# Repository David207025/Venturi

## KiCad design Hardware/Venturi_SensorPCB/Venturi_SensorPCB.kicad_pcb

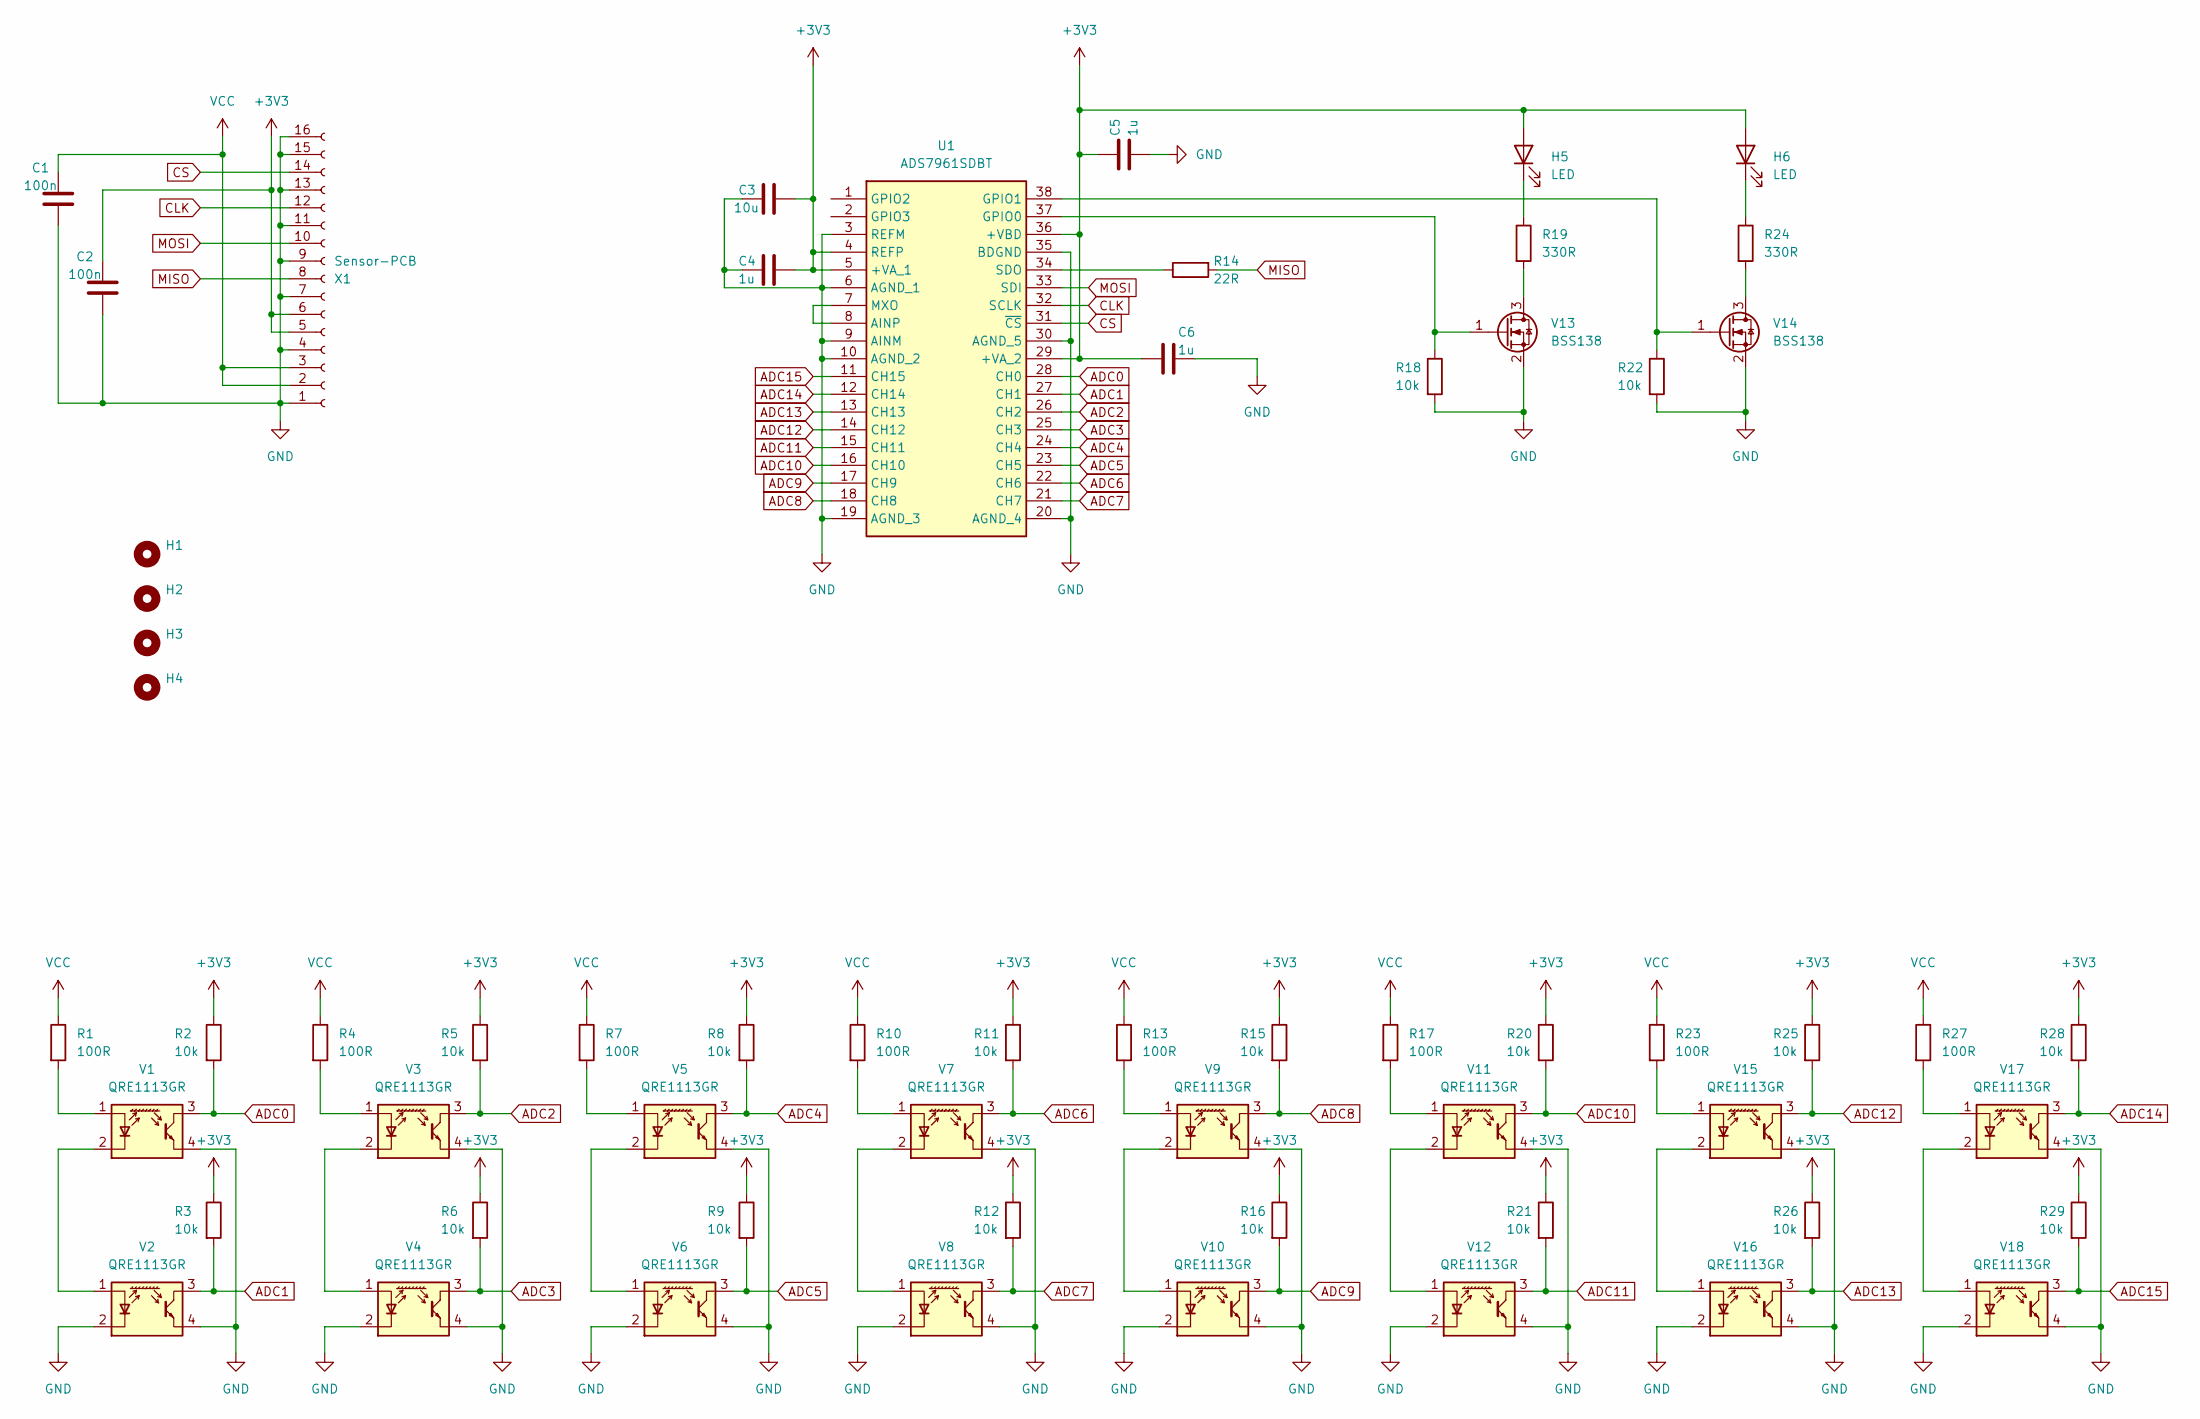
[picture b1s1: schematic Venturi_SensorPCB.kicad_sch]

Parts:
C1, C2: 100n; C_0805_2012Metric_Pad1.18x1.45mm_HandSolder
C3: 10u; C_0603_1608Metric_Pad1.08x0.95mm_HandSolder
C4, C5, C6: 1u; C_0603_1608Metric_Pad1.08x0.95mm_HandSolder
H1, H2, H3, H4: MountingHole_3.2mm_M3_DIN965
H5, H6: LED; LED_0805_2012Metric_Pad1.15x1.40mm_HandSolder
R1, R4, R7, R10, R13, R17, R23, R27: 100R; R_0603_1608Metric_Pad0.98x0.95mm_HandSolder
R2, R3, R5, R6, R8, R9, R11, R12, R15, R16, R18, R20, R21, R22, R25, R26, R28, R29: 10k; R_0603_1608Metric_Pad0.98x0.95mm_HandSolder
R14: 22R; R_0805_2012Metric_Pad1.20x1.40mm_HandSolder
R19, R24: 330R; R_0603_1608Metric_Pad0.98x0.95mm_HandSolder
U1: ADS7961SDBT; SOP50P640X120-38N; Mouser Part Number 595-ADS7961SDBT
V1, V2, V3, V4, V5, V6, V7, V8, V9, V10, V11, V12, V15, V16, V17, V18: QRE1113GR; OnSemi_CASE100CY
V13, V14: BSS138; SOT-23
X1: Sensor-PCB; SensorPCB-Connector

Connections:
+3V3: C2.1, C3.2, C4.2, C5.1, C6.1, H5.2 (A), H6.2 (A), R2.1, R3.1, R5.1, R6.1, R8.1, R9.1, R11.1, R12.1, R15.1, R16.1, R20.1, R21.1, R25.1, R26.1, R28.1, R29.1, U1.4 (REFP), U1.5 (+VA_1), U1.29 (+VA_2), U1.36 (+VBD), X1.5, X1.6
ADC0: R2.2, U1.28 (CH0), V1.3
ADC1: R3.2, U1.27 (CH1), V2.3
ADC2: R5.2, U1.26 (CH2), V3.3
ADC3: R6.2, U1.25 (CH3), V4.3
ADC4: R8.2, U1.24 (CH4), V5.3
ADC5: R9.2, U1.23 (CH5), V6.3
ADC6: R11.2, U1.22 (CH6), V7.3
ADC7: R12.2, U1.21 (CH7), V8.3
ADC8: R15.2, U1.18 (CH8), V9.3
ADC9: R16.2, U1.17 (CH9), V10.3
ADC10: R20.2, U1.16 (CH10), V11.3
ADC11: R21.2, U1.15 (CH11), V12.3
ADC12: R25.2, U1.14 (CH12), V15.3
ADC13: R26.2, U1.13 (CH13), V16.3
ADC14: R28.2, U1.12 (CH14), V17.3
ADC15: R29.2, U1.11 (CH15), V18.3
CLK: U1.32 (SCLK), X1.12
CS: U1.31 (~CS), X1.14
GND: C1.2, C2.2, C3.1, C4.1, C5.2, C6.2, R18.2, R22.2, U1.3 (REFM), U1.6 (AGND_1), U1.9 (AINM), U1.10 (AGND_2), U1.19 (AGND_3), U1.20 (AGND_4), U1.30 (AGND_5), U1.35 (BDGND), V1.4, V2.2 (K), V2.4, V3.4, V4.2 (K), V4.4, V5.4, V6.2 (K), V6.4, V7.4, V8.2 (K), V8.4, V9.4, V10.2 (K), V10.4, V11.4, V12.2 (K), V12.4, V13.2 (S), V14.2 (S), V15.4, V16.2 (K), V16.4, V17.4, V18.2 (K), V18.4, X1.1, X1.4, X1.7, X1.9, X1.11, X1.13, X1.15, X1.16
MISO: R14.2, X1.8
MOSI: U1.33 (SDI), X1.10
unnamed: H5.1 (K), R19.1
unnamed: H6.1 (K), R24.1
unnamed: U1.7 (MXO), U1.8 (AINP)
unnamed: R18.1, U1.37 (GPIO0), V13.1 (G)
unnamed: R22.1, U1.38 (GPIO1), V14.1 (G)
unnamed: R14.1, U1.34 (SDO)
unnamed: R1.2, V1.1 (A)
unnamed: V1.2 (K), V2.1 (A)
unnamed: R4.2, V3.1 (A)
unnamed: V3.2 (K), V4.1 (A)
unnamed: R7.2, V5.1 (A)
unnamed: V5.2 (K), V6.1 (A)
unnamed: R10.2, V7.1 (A)
unnamed: V7.2 (K), V8.1 (A)
unnamed: R13.2, V9.1 (A)
unnamed: V9.2 (K), V10.1 (A)
unnamed: R17.2, V11.1 (A)
unnamed: V11.2 (K), V12.1 (A)
unnamed: R19.2, V13.3 (D)
unnamed: R24.2, V14.3 (D)
unnamed: R23.2, V15.1 (A)
unnamed: V15.2 (K), V16.1 (A)
unnamed: R27.2, V17.1 (A)
unnamed: V17.2 (K), V18.1 (A)
VCC: C1.1, R1.1, R4.1, R7.1, R10.1, R13.1, R17.1, R23.1, R27.1, X1.2, X1.3

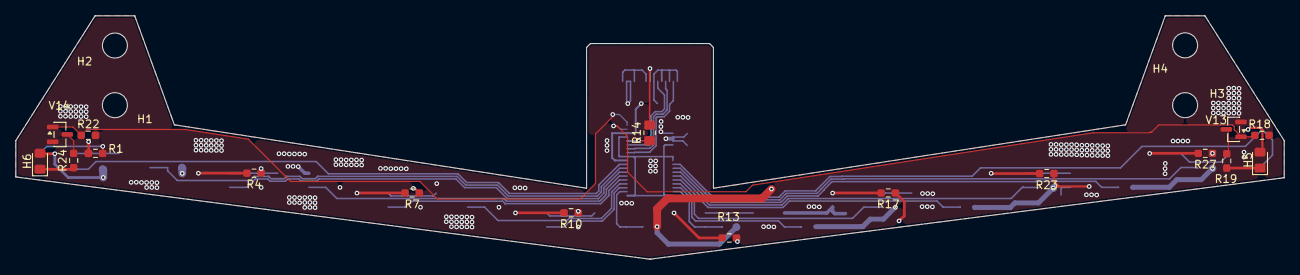
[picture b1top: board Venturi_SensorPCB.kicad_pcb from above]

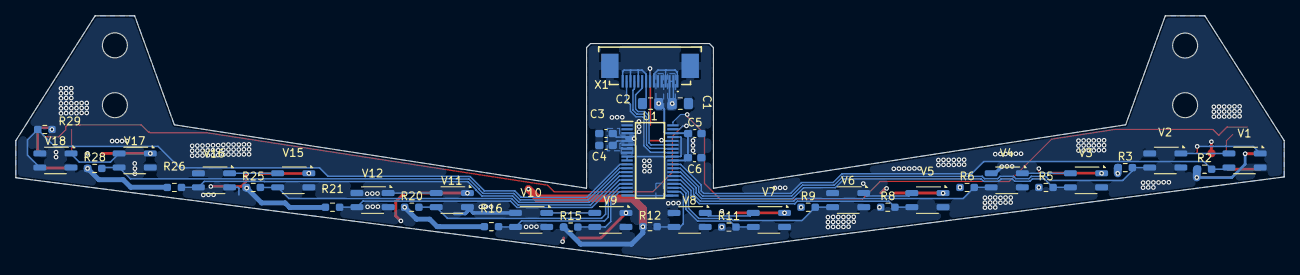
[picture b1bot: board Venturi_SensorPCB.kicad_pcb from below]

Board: 4 copper layers, 162.6 x 31.2 mm, 61 parts (40 on the bottom side), 47 nets.

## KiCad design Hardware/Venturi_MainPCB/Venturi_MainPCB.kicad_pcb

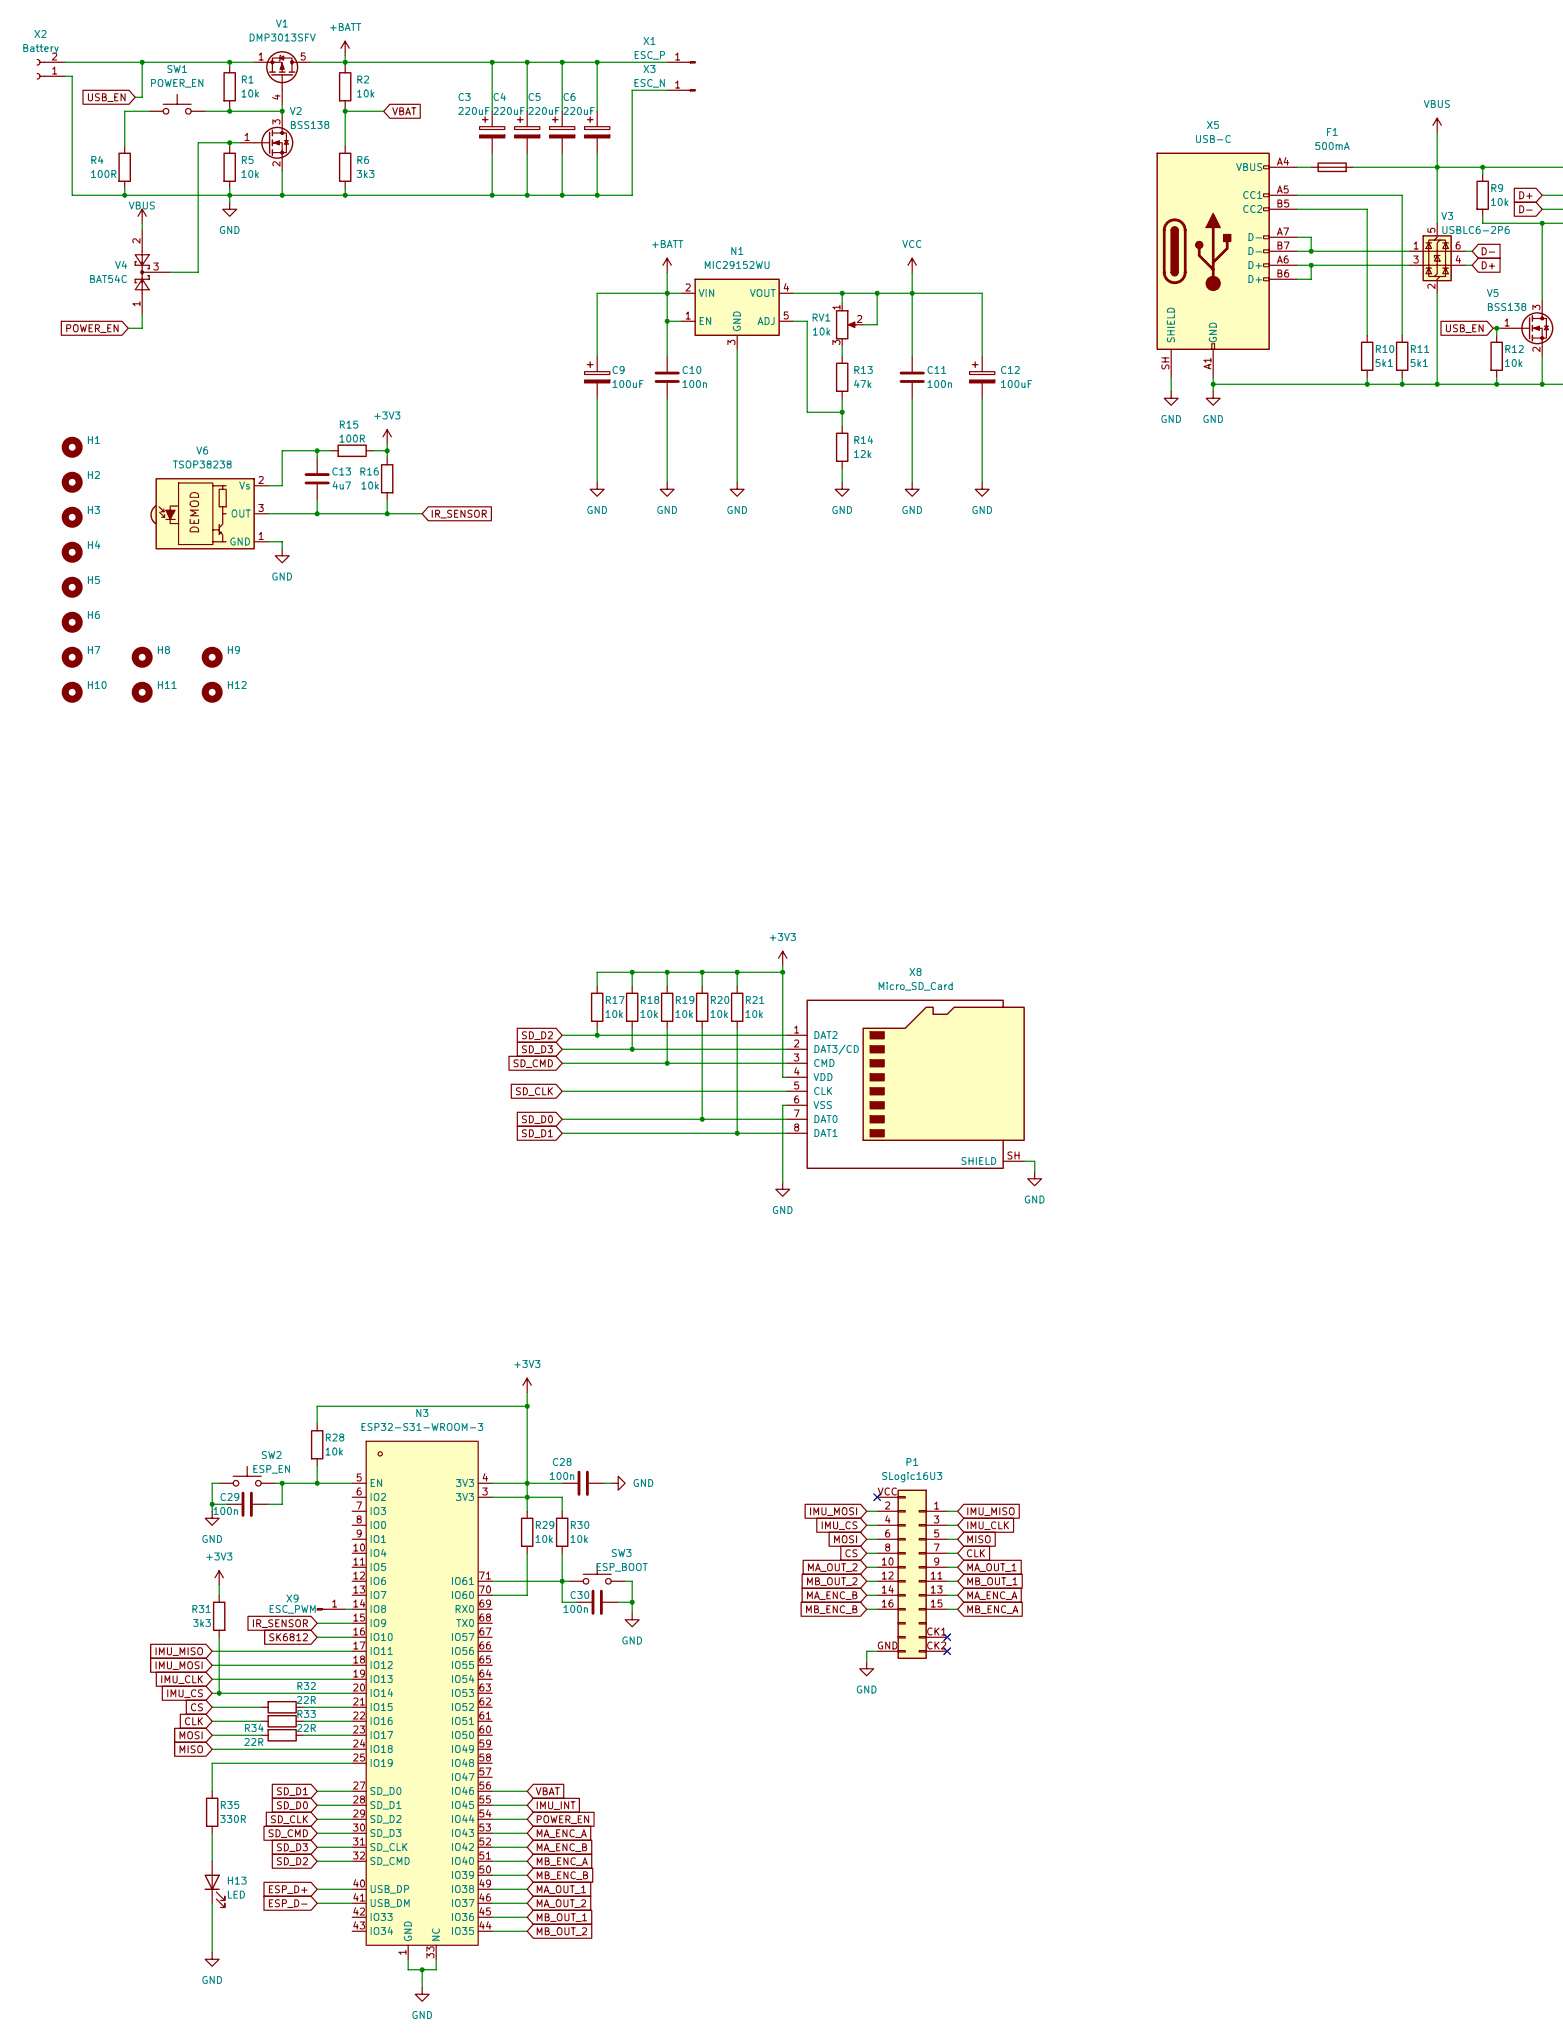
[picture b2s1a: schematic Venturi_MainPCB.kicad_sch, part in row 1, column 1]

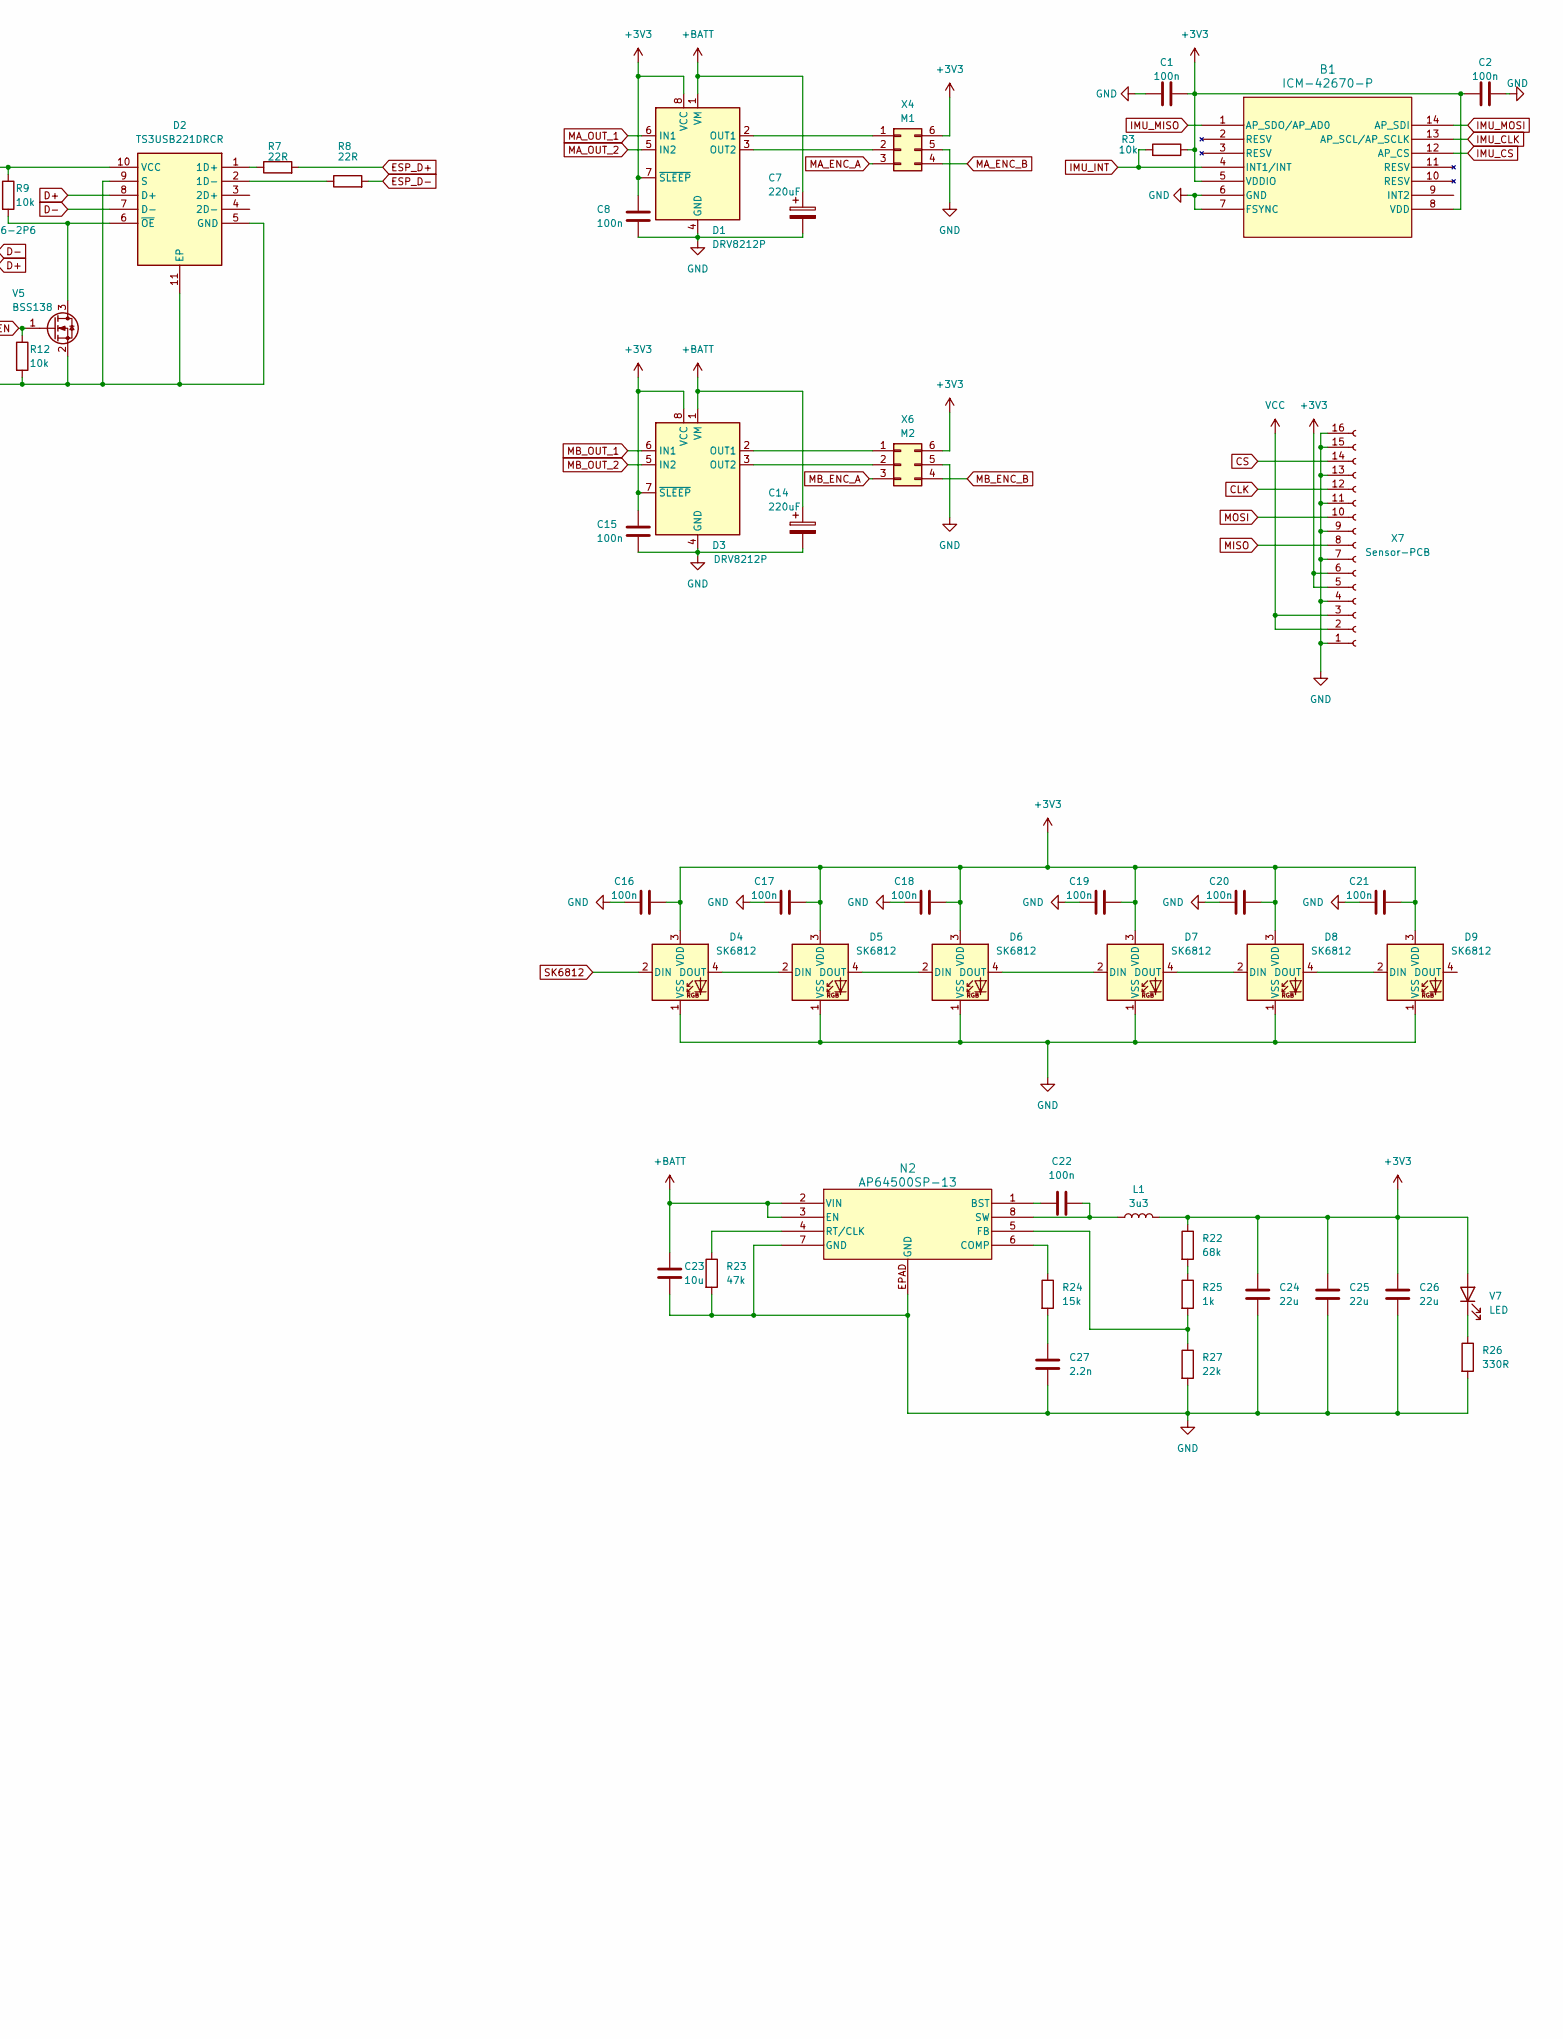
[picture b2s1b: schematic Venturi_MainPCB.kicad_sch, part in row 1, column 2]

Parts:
B1: ICM-42670-P; LGA-14_3x2.5mm_P0.5mm_LayoutBorder3x4y
C1, C2, C8, C10, C11, C15, C16, C17, C18, C19, C20, C21, C28, C29, C30: 100n; C_0805_2012Metric_Pad1.18x1.45mm_HandSolder
C3, C4, C5, C6, C7, C14: 220uF; CP_Elec_6.3x9.9
C9, C12: 100uF; CP_EIA-7343-15_Kemet-W_HandSolder
C13: 4u7; C_0805_2012Metric_Pad1.18x1.45mm_HandSolder
C22: 100n; C_0603_1608Metric_Pad1.08x0.95mm_HandSolder
C23: 10u; C_0603_1608Metric_Pad1.08x0.95mm_HandSolder
C24, C25, C26: 22u; C_0603_1608Metric_Pad1.08x0.95mm_HandSolder
C27: 2.2n; C_0603_1608Metric_Pad1.08x0.95mm_HandSolder
D1, D3: DRV8212P; WSON-8-1EP_2x2mm_P0.5mm_EP0.9x1.6mm_ThermalVias
D2: TS3USB221DRCR; SON50P300X300X100-11N-D; Mouser Part Number 595-TS3USB221DRCR
D4, D5, D6, D7, D8, D9: SK6812; LED_SK6812_PLCC4_5.0x5.0mm_P3.2mm
F1: 500mA; Fuse_0805_2012Metric_Pad1.15x1.40mm_HandSolder
H1, H2, H3, H4, H5, H6, H7, H8, H9, H10, H11, H12: MountingHole_3.2mm_M3_DIN965
H13: LED; LED_0805_2012Metric_Pad1.15x1.40mm_HandSolder
L1: 3u3; L_Vishay_IHLP-1616
N1: MIC29152WU; TO-252-5_TabPin3
N2: AP64500SP-13; SO-8EP_DIO
N3: ESP32-S31-WROOM-3; MPN ESP32-S31-WROOM-3; LCSC Part C9900281993
P1: SLogic16U3
R1, R2, R3, R5, R16, R17, R18, R19, R20, R21, R28, R29, R30: 10k; R_0805_2012Metric_Pad1.20x1.40mm_HandSolder
R4, R15: 100R; R_0805_2012Metric_Pad1.20x1.40mm_HandSolder
R6, R31: 3k3; R_0805_2012Metric_Pad1.20x1.40mm_HandSolder
R7, R8, R32, R33, R34: 22R; R_0805_2012Metric_Pad1.20x1.40mm_HandSolder
R9, R12: 10k; R_0603_1608Metric_Pad0.98x0.95mm_HandSolder
R10, R11: 5k1; R_0805_2012Metric_Pad1.20x1.40mm_HandSolder
R13: 47k; R_0805_2012Metric_Pad1.20x1.40mm_HandSolder
R14: 12k; R_0805_2012Metric_Pad1.20x1.40mm_HandSolder
R22: 68k; R_0603_1608Metric_Pad0.98x0.95mm_HandSolder
R23: 47k; R_0603_1608Metric_Pad0.98x0.95mm_HandSolder
R24: 15k; R_0603_1608Metric_Pad0.98x0.95mm_HandSolder
R25: 1k; R_0603_1608Metric_Pad0.98x0.95mm_HandSolder
R26: 330R; R_0603_1608Metric_Pad0.98x0.95mm_HandSolder
R27: 22k; R_0603_1608Metric_Pad0.98x0.95mm_HandSolder
R35: 330R; R_0805_2012Metric_Pad1.20x1.40mm_HandSolder
RV1: 10k; Potentiometer_Bourns_3314J_Vertical
SW1: POWER_EN; SW_SPST_Omron_B3FS-100xP
SW2: ESP_EN; SW_SPST_Omron_B3FS-100xP
SW3: ESP_BOOT; SW_SPST_Omron_B3FS-100xP
V1: DMP3013SFV; Diodes_PowerDI3333-8
V2, V5: BSS138; SOT-23
V3: USBLC6-2P6; SOT-666
V4: BAT54C; SOT-23
V6: TSOP38238; Vishay_CAST-3Pin
V7: LED; LED_0805_2012Metric_Pad1.15x1.40mm_HandSolder
X1: ESC_P; SolderWire-0.25sqmm_1x01_D0.65mm_OD1.7mm
X2: Battery; AMASS_XT30U-M_1x02_P5.0mm_Vertical
X3: ESC_N; SolderWire-0.25sqmm_1x01_D0.65mm_OD1.7mm
X4: M1; PinHeader_2x03_P2.54mm_Vertical_SMD
X5: USB-C; USB_C_Receptacle_G-Switch_GT-USB-7010ASV
X6: M2; PinHeader_2x03_P2.54mm_Vertical_SMD
X7: Sensor-PCB; SensorPCB-Connector
X8: Micro_SD_Card; microSD_HC_Wuerth_693072010801
X9: ESC_PWM; SolderWire-0.25sqmm_1x01_D0.65mm_OD1.7mm

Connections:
+3V3: B1.5 (VDDIO), B1.8 (VDD), C1.1, C2.2, C8.1, C15.1, C16.2, C17.2, C18.2, C19.2, C20.2, C21.2, C24.2, C25.2, C26.2, C28.1, D1.7 (~SLEEP), D1.8 (VCC), D3.7 (~SLEEP), D3.8 (VCC), D4.3 (VDD), D5.3 (VDD), D6.3 (VDD), D7.3 (VDD), D8.3 (VDD), D9.3 (VDD), L1.2, N3.3 (3V3), N3.4 (3V3), R3.1, R15.1, R16.1, R17.1, R18.1, R19.1, R20.1, R21.1, R22.1, R28.1, R29.1, R30.1, R31.1, V7.2 (A), X4.6, X6.6, X7.5, X7.6, X8.4 (VDD)
+BATT: C3.1, C4.1, C5.1, C6.1, C7.1, C9.1, C10.1, C14.1, C23.2, D1.1 (VM), D3.1 (VM), N1.1 (EN), N1.2 (VIN), N2.2 (VIN), N2.3 (EN), R2.1, V1.5 (D), X1.1 (Pin_1_1)
CLK: P1.7, R33.2, X7.12
CS: P1.8, R32.2, X7.14
D+: D2.8 (D+), V3.4 (I/O2)
D-: D2.7 (D-), V3.6 (I/O1)
ESP_D+: N3.40 (USB_DP), R7.2
ESP_D-: N3.41 (USB_DM), R8.2
GND: B1.6 (GND), B1.7 (FSYNC), C1.2, C2.1, C3.2, C4.2, C5.2, C6.2, C7.2, C8.2, C9.2, C10.2, C11.2, C12.2, C14.2, C15.2, C16.1, C17.1, C18.1, C19.1, C20.1, C21.1, C23.1, C24.1, C25.1, C26.1, C27.2, C28.2, C29.1, C30.2, D1.4 (GND), D1.9 (GND), D2.5 (GND), D2.9 (S), D2.11 (EP), D3.4 (GND), D3.9 (GND), D4.1 (VSS), D5.1 (VSS), D6.1 (VSS), D7.1 (VSS), D8.1 (VSS), D9.1 (VSS), H13.1 (K), N1.3 (GND), N2.7 (GND), N2.EPAD (GND), N3.1 (GND), N3.2 (GND), N3.26 (GND), N3.33 (NC), N3.34 (NC), N3.35 (NC), N3.36 (NC), N3.37 (NC), N3.38 (NC), N3.39 (NC), N3.47 (GND), N3.48 (GND), N3.72 (GND), N3.73 (GND), N3.74 (GND), N3.75 (GND), N3.76 (GND), N3.77 (GND), N3.78 (GND), N3.79 (GND), N3.80 (GND), N3.81 (GND), N3.82 (GND), N3.83 (GND), N3.84 (GND), N3.85 (GND), N3.86 (GND), N3.87 (GND), N3.88 (GND), N3.89 (GND), N3.90 (GND), N3.91 (NC), N3.92 (GND), N3.93 (GND), N3.94 (GND), N3.95 (GND), N3.96 (GND), N3.97 (GND), N3.98 (GND), N3.99 (GND), P1.GND, R4.2, R5.2, R6.2, R10.2, R11.2, R12.2, R14.2, R23.2, R26.2, R27.2, SW2.1, SW3.2, V2.2 (S), V3.2 (GND), V5.2 (S), V6.1 (GND), X2.1, X3.1 (Pin_1_1), X4.5, X5.A1 (GND), X5.A12 (GND), X5.B1 (GND), X5.B12 (GND), X5.SH (SHIELD), X6.5, X7.1, X7.4, X7.7, X7.9, X7.11, X7.13, X7.15, X7.16, X8.6 (VSS), X8.SH (SHIELD)
IMU_CLK: B1.13 (AP_SCL/AP_SCLK), N3.19 (IO13), P1.3
IMU_CS: B1.12 (AP_CS), N3.20 (IO14), P1.4, R31.2
IMU_INT: B1.4 (INT1/INT), N3.55 (IO45), R3.2
IMU_MISO: B1.1 (AP_SDO/AP_AD0), N3.17 (IO11), P1.1
IMU_MOSI: B1.14 (AP_SDI), N3.18 (IO12), P1.2
IR_SENSOR: C13.1, N3.15 (IO9), R16.2, V6.3 (OUT)
MA_ENC_A: N3.53 (IO43), P1.13, X4.3
MA_ENC_B: N3.52 (IO42), P1.14, X4.4
MA_OUT_1: D1.6 (IN1), N3.49 (IO38), P1.9
MA_OUT_2: D1.5 (IN2), N3.46 (IO37), P1.10
MB_ENC_A: N3.51 (IO40), P1.15, X6.3
MB_ENC_B: N3.50 (IO39), P1.16, X6.4
MB_OUT_1: D3.6 (IN1), N3.45 (IO36), P1.11
MB_OUT_2: D3.5 (IN2), N3.44 (IO35), P1.12
MISO: N3.24 (IO18), P1.5, X7.8
MOSI: P1.6, R34.2, X7.10
unnamed: C27.1, R24.2
unnamed: D1.2 (OUT1), X4.1
unnamed: D1.3 (OUT2), X4.2
unnamed: D2.1 (1D+), R7.1
unnamed: D2.2 (1D-), R8.1
unnamed: D2.6 (~OE), R9.2, V5.3 (D)
unnamed: D3.2 (OUT1), X6.1
unnamed: D3.3 (OUT2), X6.2
unnamed: D4.4 (DOUT), D5.2 (DIN)
unnamed: D5.4 (DOUT), D6.2 (DIN)
unnamed: D6.4 (DOUT), D7.2 (DIN)
unnamed: D7.4 (DOUT), D8.2 (DIN)
unnamed: D8.4 (DOUT), D9.2 (DIN)
unnamed: F1.1, X5.A4 (VBUS), X5.A9 (VBUS), X5.B4 (VBUS), X5.B9 (VBUS)
unnamed: H13.2 (A), R35.2
unnamed: N1.5 (ADJ), R13.2, R14.1
unnamed: C22.1, N2.1 (BST)
unnamed: N2.6 (COMP), R24.1
unnamed: N2.5 (FB), R25.2, R27.1
unnamed: N2.4 (RT/CLK), R23.1
unnamed: C22.2, L1.1, N2.8 (SW)
unnamed: C29.2, N3.5 (EN), R28.2, SW2.2
unnamed: N3.14 (IO8), X9.1 (Pin_1_1)
unnamed: N3.21 (IO15), R32.1
unnamed: N3.22 (IO16), R33.1
unnamed: N3.23 (IO17), R34.1
unnamed: N3.25 (IO19), R35.1
unnamed: N3.70 (IO60), R29.2
unnamed: C30.1, N3.71 (IO61), R30.2, SW3.1
unnamed: R4.1, SW1.1
unnamed: R13.1, RV1.3
unnamed: R22.2, R25.1
unnamed: R1.2, SW1.2, V1.4 (G), V2.3 (D)
unnamed: R5.1, V2.1 (G), V4.3
unnamed: V3.1 (I/O1), X5.A7 (D-), X5.B7 (D-)
unnamed: V3.3 (I/O2), X5.A6 (D+), X5.B6 (D+)
unnamed: C13.2, R15.2, V6.2 (Vs)
unnamed: R26.1, V7.1 (K)
unnamed: R11.1, X5.A5 (CC1)
unnamed: R10.1, X5.B5 (CC2)
POWER_EN: N3.54 (IO44), V4.1
SD_CLK: N3.29 (SD_D2), X8.5 (CLK)
SD_CMD: N3.30 (SD_D3), R19.2, X8.3 (CMD)
SD_D0: N3.28 (SD_D1), R20.2, X8.7 (DAT0)
SD_D1: N3.27 (SD_D0), R21.2, X8.8 (DAT1)
SD_D2: N3.32 (SD_CMD), R17.2, X8.1 (DAT2)
SD_D3: N3.31 (SD_CLK), R18.2, X8.2 (DAT3/CD)
SK6812: D4.2 (DIN), N3.16 (IO10)
USB_EN: R1.1, R12.1, V1.1 (S), V1.2 (S), V1.3 (S), V5.1 (G), X2.2
VBAT: N3.56 (IO46), R2.2, R6.1
VBUS: D2.10 (VCC), F1.2, R9.1, V3.5 (VBUS), V4.2
VCC: C11.1, C12.1, N1.4 (VOUT), RV1.1, RV1.2, X7.2, X7.3

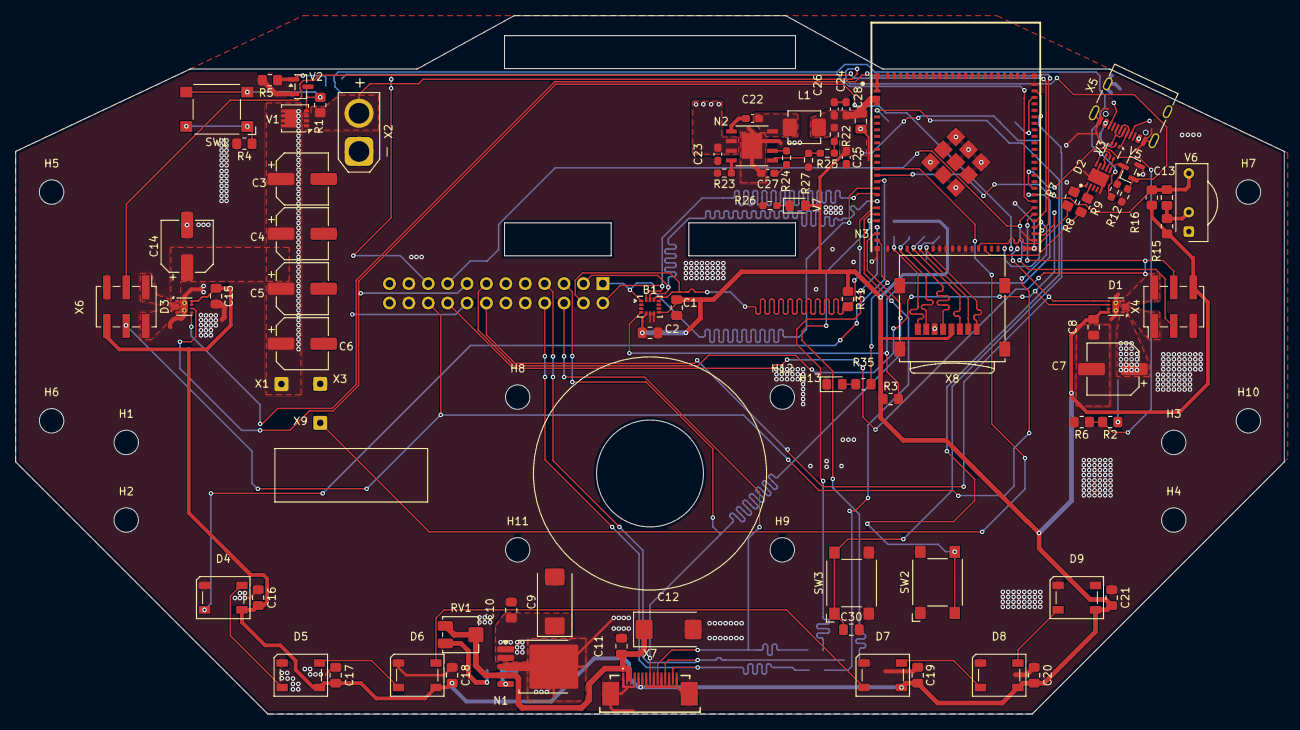
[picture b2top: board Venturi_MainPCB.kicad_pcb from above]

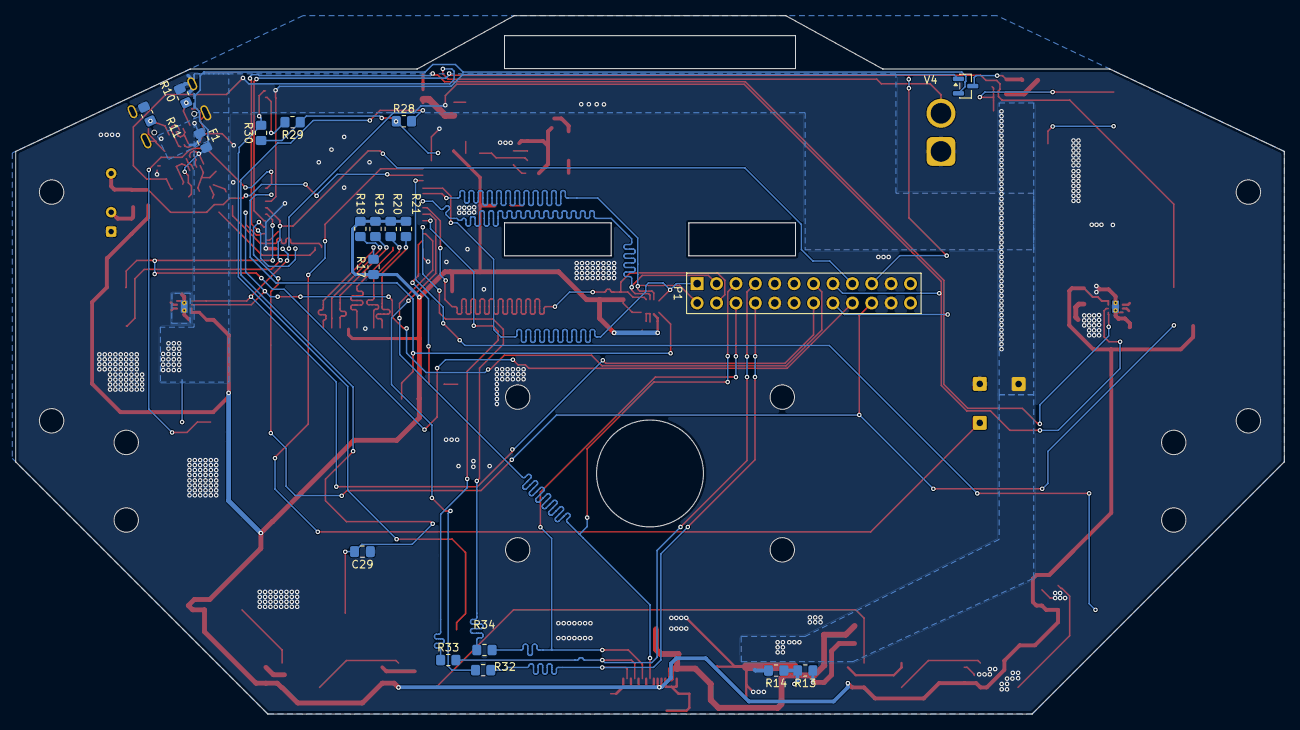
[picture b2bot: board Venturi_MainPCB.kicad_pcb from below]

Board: 4 copper layers, 166.1 x 91.4 mm, 114 parts (19 on the bottom side), 77 nets.

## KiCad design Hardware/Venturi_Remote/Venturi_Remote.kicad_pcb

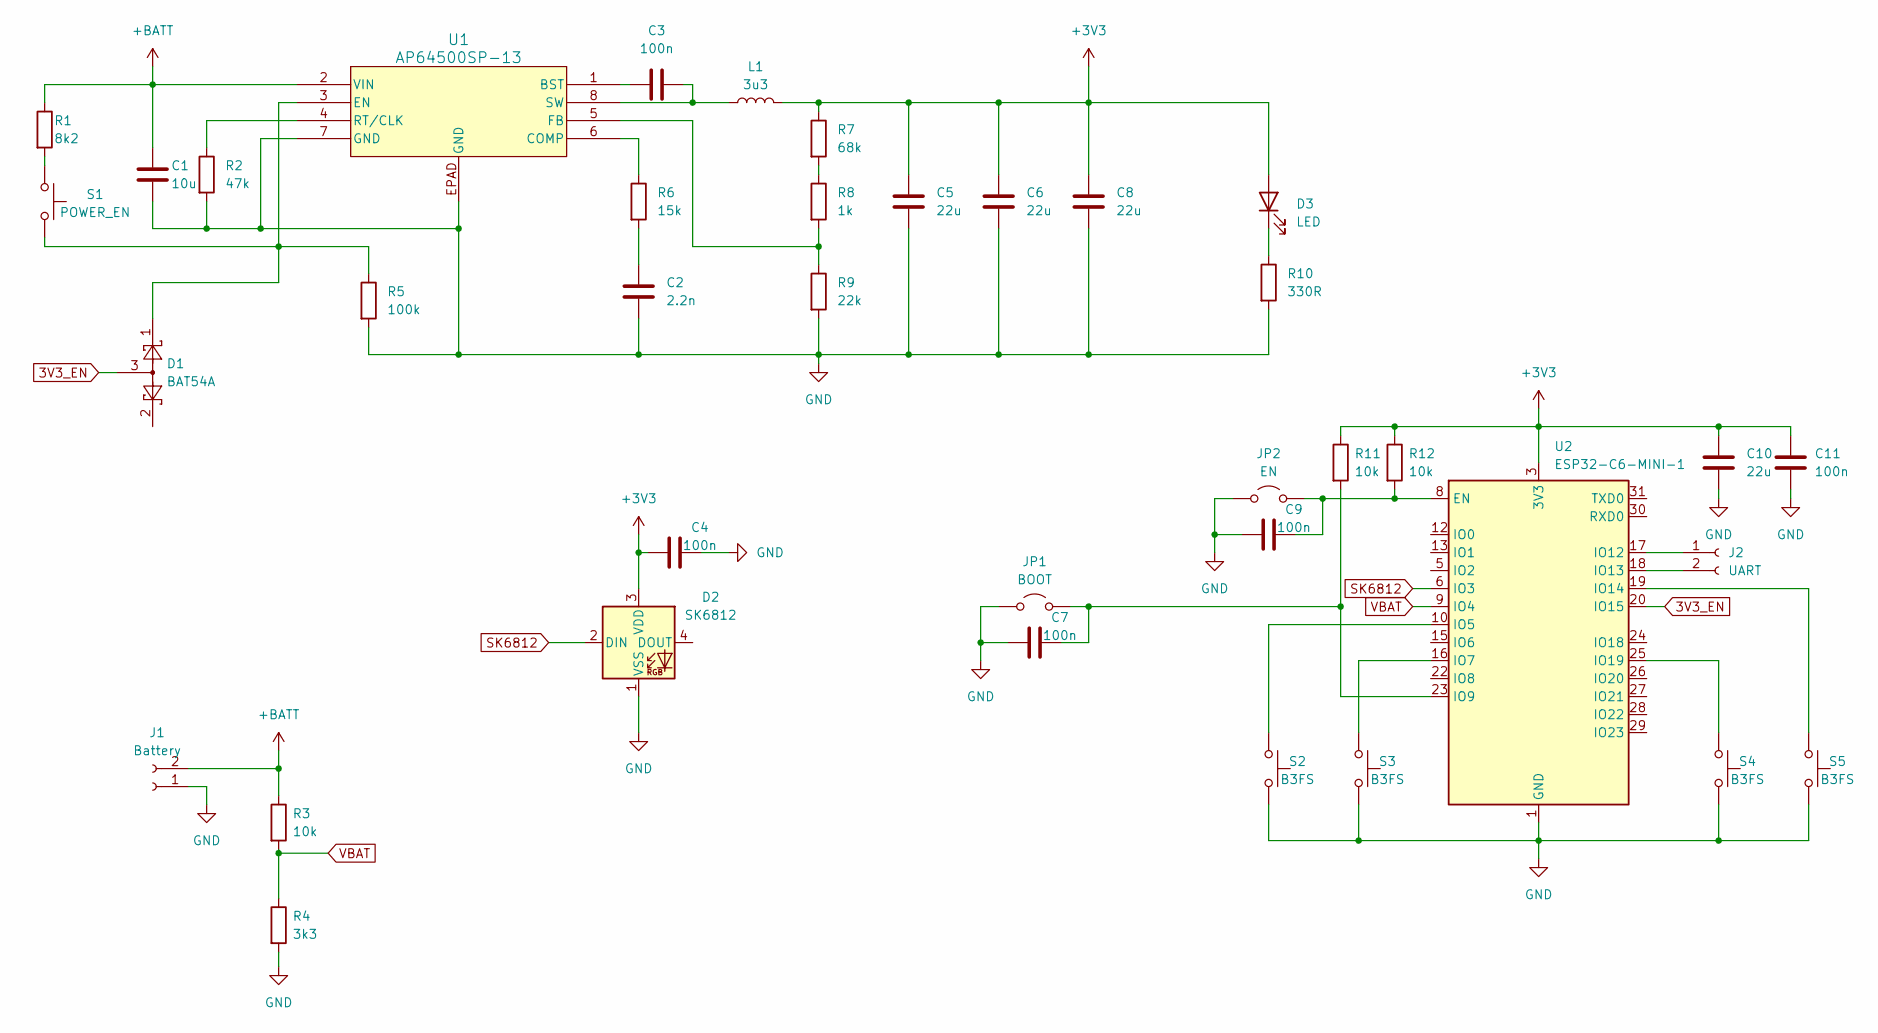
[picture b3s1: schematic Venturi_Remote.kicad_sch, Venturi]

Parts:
C1: 10u; C_0805_2012Metric_Pad1.18x1.45mm_HandSolder
C2: 2.2n; C_0805_2012Metric_Pad1.18x1.45mm_HandSolder
C3, C4, C7, C9, C11: 100n; C_0805_2012Metric_Pad1.18x1.45mm_HandSolder
C5, C6, C8, C10: 22u; C_0805_2012Metric_Pad1.18x1.45mm_HandSolder
D1: BAT54A; SOT-23
D2: SK6812; LED_SK6812_PLCC4_5.0x5.0mm_P3.2mm
D3: LED; LED_0805_2012Metric_Pad1.15x1.40mm_HandSolder
J1: Battery; AMASS_XT30U-M_1x02_P5.0mm_Vertical
J2: UART; PinSocket_1x02_P2.54mm_Vertical
JP1: BOOT; SolderJumper-2_P1.3mm_Open_Pad1.0x1.5mm
JP2: EN; SolderJumper-2_P1.3mm_Open_Pad1.0x1.5mm
L1: 3u3; L_Vishay_IHLP-1616
R1: 8k2; R_0805_2012Metric_Pad1.20x1.40mm_HandSolder
R2: 47k; R_0805_2012Metric_Pad1.20x1.40mm_HandSolder
R3, R11, R12: 10k; R_0805_2012Metric_Pad1.20x1.40mm_HandSolder
R4: 3k3; R_0805_2012Metric_Pad1.20x1.40mm_HandSolder
R5: 100k; R_0805_2012Metric_Pad1.20x1.40mm_HandSolder
R6: 15k; R_0805_2012Metric_Pad1.20x1.40mm_HandSolder
R7: 68k; R_0805_2012Metric_Pad1.20x1.40mm_HandSolder
R8: 1k; R_0805_2012Metric_Pad1.20x1.40mm_HandSolder
R9: 22k; R_0805_2012Metric_Pad1.20x1.40mm_HandSolder
R10: 330R; R_0805_2012Metric_Pad1.20x1.40mm_HandSolder
S1: POWER_EN; SW_SPST_Omron_B3FS-105xP
S2, S3, S4, S5: B3FS; SW_SPST_Omron_B3FS-105xP
U1: AP64500SP-13; SO-8EP_DIO
U2: ESP32-C6-MINI-1

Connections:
3V3_EN: D1.3, U2.20 (IO15)
+3V3: C4.2, C5.2, C6.2, C8.2, C10.2, C11.2, D2.3 (VDD), D3.2 (A), L1.2, R7.1, R11.1, R12.1, U2.3 (3V3)
+BATT: C1.2, J1.2, R1.1, R3.1, U1.2 (VIN)
GND: C1.1, C2.1, C4.1, C5.1, C6.1, C7.2, C8.1, C9.2, C10.1, C11.1, D2.1 (VSS), J1.1, JP1.1 (A), JP2.1 (A), R2.2, R4.2, R5.2, R9.2, R10.2, S2.2, S3.2, S4.2, S5.2, U1.7 (GND), U1.EPAD (GND), U2.1 (GND), U2.2 (GND), U2.11 (GND), U2.14 (GND), U2.36 (GND), U2.37 (GND), U2.38 (GND), U2.39 (GND), U2.40 (GND), U2.41 (GND), U2.42 (GND), U2.43 (GND), U2.44 (GND), U2.45 (GND), U2.46 (GND), U2.47 (GND), U2.48 (GND), U2.49 (GND), U2.50 (GND), U2.51 (GND), U2.52 (GND), U2.53 (GND)
unnamed: C2.2, R6.2
unnamed: D3.1 (K), R10.1
unnamed: J2.1, U2.17 (IO12)
unnamed: J2.2, U2.18 (IO13)
unnamed: C7.1, JP1.2 (B), R11.2, U2.23 (IO9)
unnamed: C9.1, JP2.2 (B), R12.2, U2.8 (EN)
unnamed: R1.2, S1.1
unnamed: R7.2, R8.1
unnamed: C3.1, U1.1 (BST)
unnamed: R6.1, U1.6 (COMP)
unnamed: D1.1, R5.1, S1.2, U1.3 (EN)
unnamed: R8.2, R9.1, U1.5 (FB)
unnamed: R2.1, U1.4 (RT/CLK)
unnamed: C3.2, L1.1, U1.8 (SW)
unnamed: S2.1, U2.10 (IO5)
unnamed: S3.1, U2.16 (IO7)
unnamed: S5.1, U2.19 (IO14)
unnamed: S4.1, U2.25 (IO19)
SK6812: D2.2 (DIN), U2.6 (IO3)
VBAT: R3.2, R4.1, U2.9 (IO4)
